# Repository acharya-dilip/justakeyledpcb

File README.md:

# This PCB is consists of four buttons and 4 LED's along with a buzzer which does diffrent things from broadcasting various morse code messages and also can act as a fun memory testing game depending on what keys you press

# Schematic

# Front View of PCB

# Back View of PCB

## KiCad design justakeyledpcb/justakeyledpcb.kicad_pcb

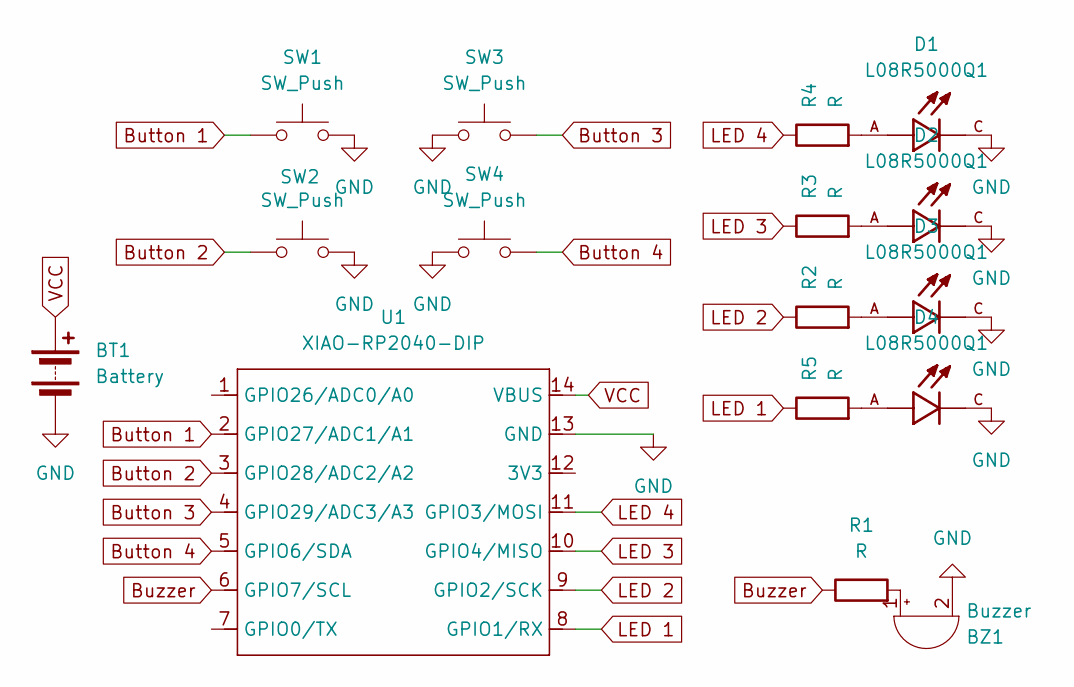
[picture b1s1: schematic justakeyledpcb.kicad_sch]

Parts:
BT1: Battery; TestPoint_2Pads_Pitch2.54mm_Drill0.8mm
BZ1: Buzzer; Buzzer_12x9.5RM7.6
D1, D2, D3, D4: L08R5000Q1; LEDRD254W57D500H1070; PARTREV NA
R1, R2, R3, R4, R5: R; R_Axial_DIN0207_L6.3mm_D2.5mm_P7.62mm_Horizontal
SW1, SW2, SW3, SW4: SW_Push; SW_Cherry_MX_1.00u_PCB
U1: XIAO-RP2040-DIP

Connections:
Button 1: SW1.1, U1.2 (GPIO27/ADC1/A1)
Button 2: SW2.1, U1.3 (GPIO28/ADC2/A2)
Button 3: SW3.1, U1.4 (GPIO29/ADC3/A3)
Button 4: SW4.1, U1.5 (GPIO6/SDA)
Buzzer: R1.1, U1.6 (GPIO7/SCL)
GND: BT1.2 (-), BZ1.2 (-), D1.C, D2.C, D3.C, D4.C, SW1.2, SW2.2, SW3.2, SW4.2, U1.13 (GND)
LED 1: R5.1, U1.8 (GPIO1/RX)
LED 2: R2.1, U1.9 (GPIO2/SCK)
LED 3: R3.1, U1.10 (GPIO4/MISO)
LED 4: R4.1, U1.11 (GPIO3/MOSI)
unnamed: BZ1.1 (+), R1.2
unnamed: D1.A, R4.2
unnamed: D2.A, R3.2
unnamed: D3.A, R2.2
unnamed: D4.A, R5.2
VCC: BT1.1 (+), U1.14 (VBUS)

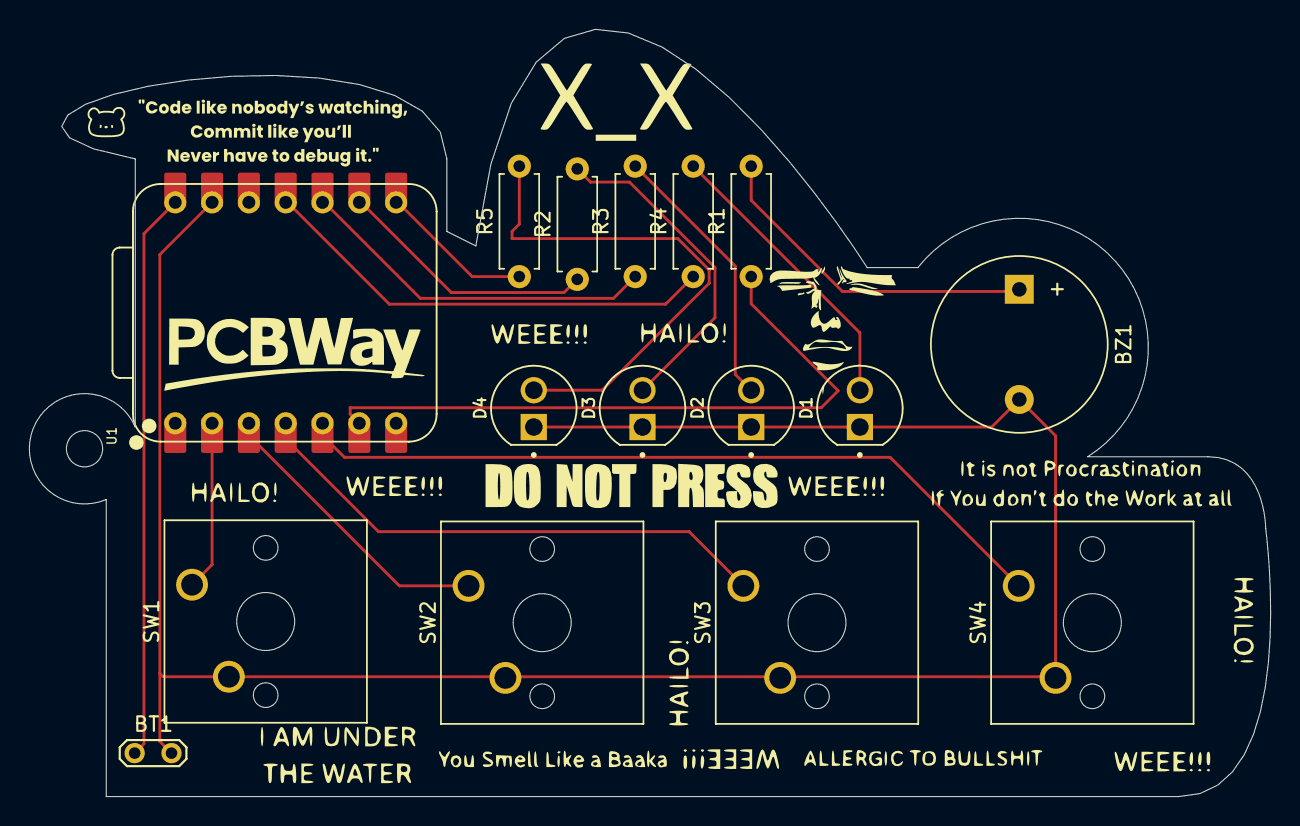
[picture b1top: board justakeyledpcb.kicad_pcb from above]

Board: 2 copper layers, 85.7 x 52.9 mm, 16 parts (0 on the bottom side), 16 nets.

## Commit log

2025-07-29 Prepared the schmatic for the PCB
2025-07-29 The Schematic is Finalised
2025-07-29 Edge Cuts is Prepared and layout is finalised for PCB
2025-07-29 Added the LED's footprints properly
2025-07-29 FInalised the PCB Schematics and PCB Layout
2025-07-29 Completely Finalised the PCB except the silkscreen
2025-07-30 Adding some stuff
2025-07-30 removed a button I thought I'd use it to start a board
2025-07-30 Cleared the A0 pin for ard seeding for random num and moved the pin downwards
2025-07-30 updated the PCB accordingly to the schematic
2025-07-30 updated the PCB accordingly to the schematic again and saved it
2025-07-30 Created a random buttonsequence generator
2025-07-30 Added the Random sequence Button lighting thingy
2025-07-30 Added the buzzer beep thing when a button press detected
2025-07-30 Made it so that if button isn't pressed within 1 sec the game ends with a beep
2025-07-30 Polished the Firmware code
2025-07-30 edited the pins to setup from array
2025-07-30 The Code Was Compiled Successfully
2025-07-30 Changed the way led pinModed
2025-07-30 the Code Compiled
2025-07-30 will try to add increments in the led's memory test
2025-07-30 Added the increment system where one more led flashes after one round is successfully complted
2025-07-31 Planning to add a nay nay niga nay song beats
2025-07-31 Scrapped the song beats idea added the SOS signal broadcasting
2025-07-31 added the place for an external power source in the PCB schem and updated the PCB design
2025-07-31 Updated the Shape of the PCB
2025-07-31 had fun with the beizure curve thingy
2025-07-31 added the silkscreen
2025-07-31 Updated some comments in the code
2025-07-31 Added a functionality when all 4 buttons are pressed
2025-07-31 Did some debugging
2025-07-31 Added another morse code msg
2025-07-31 Created alot of functions
2025-07-31 Added a placeholder for future features when pressing button 2 and 4
2025-07-31 Final Commit
2025-07-31 Created the production files
